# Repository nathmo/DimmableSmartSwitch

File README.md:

DimmableSmartSwitch

This repo contains the schematic and the layout for an ESP32 based
dual channel smart dimmer.
The ESP32 is intended to run under ESP-easy (a firmware that with native support of MQTT and wifi).
This smart dimmer work for Inductive and Capacitive load both in AC or DC.
The circuit is triggered on crossing zero (if the Load power supply is AC)
The circuit contains a current sensing circuitery on both channel, 2 capacitive touch input and
a microphone to stream audio for voice recognition (on another device (like a raspberry pi)) and obviously the circuitery to dim the load
A PLC transcienver may be added in futur revision
(PLC transcienver : A chip that allow to transmit data over power line)

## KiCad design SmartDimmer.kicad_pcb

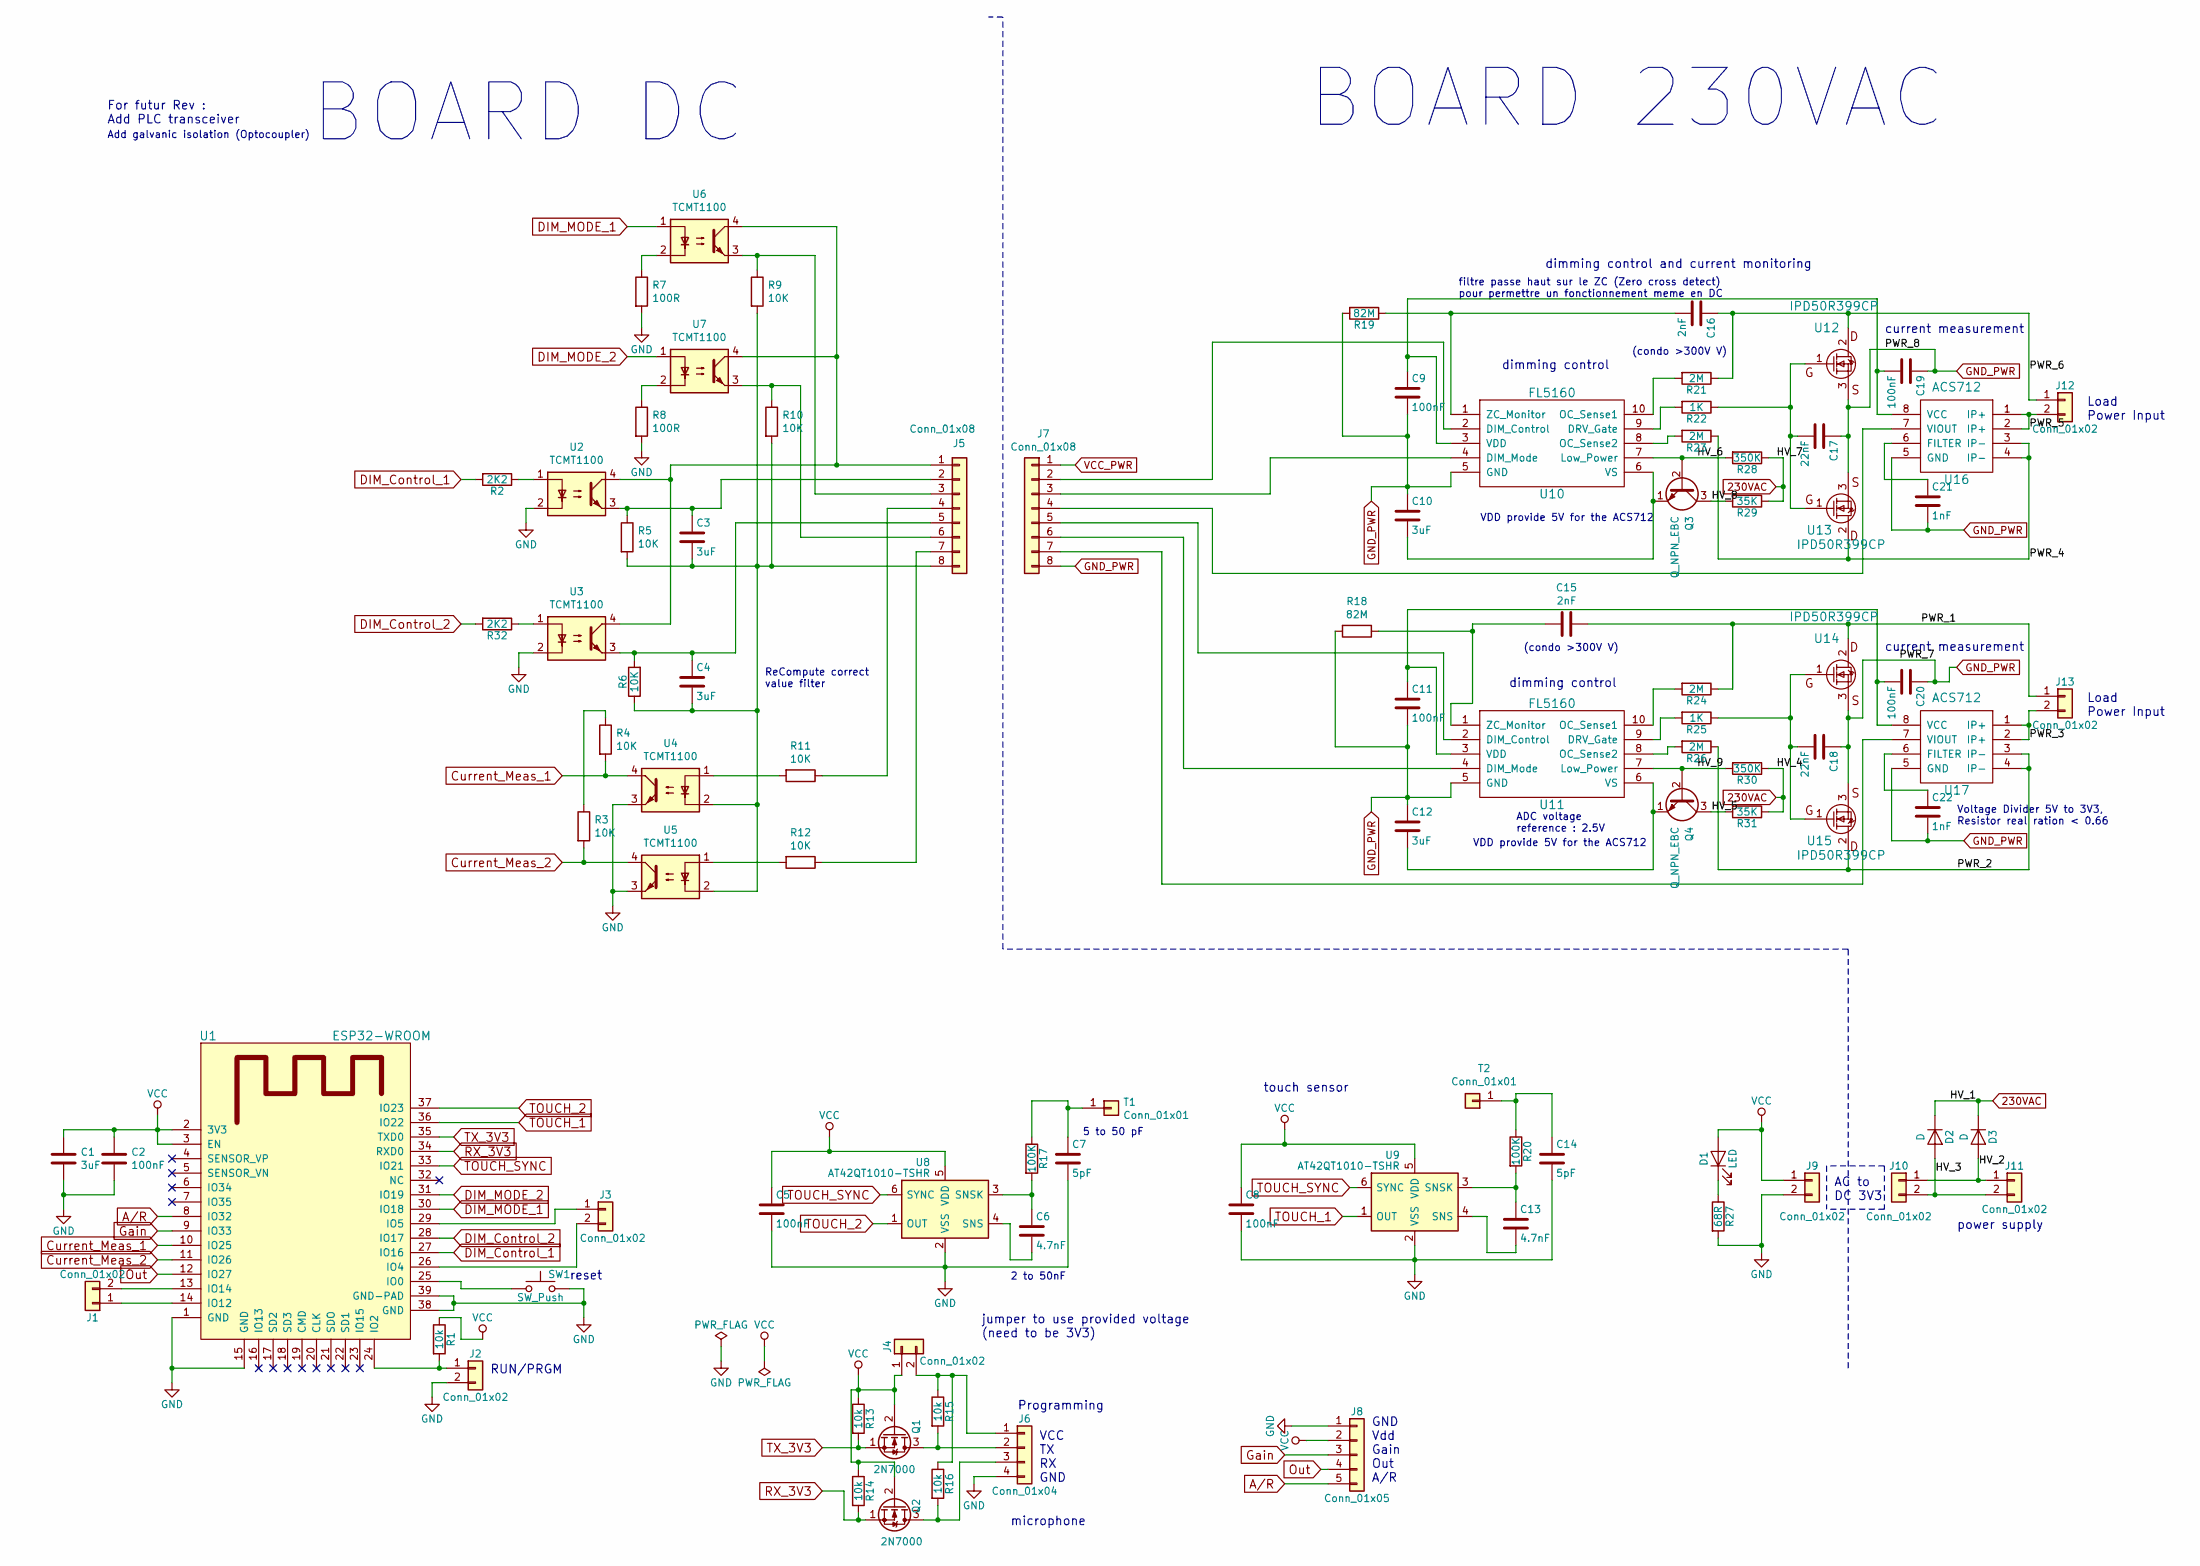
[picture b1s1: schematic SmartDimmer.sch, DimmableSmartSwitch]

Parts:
C1, C3, C4, C10, C12: 3uF; C_1206_3216Metric_Pad1.42x1.75mm_HandSolder
C2, C5, C8, C9, C11, C19, C20: 100nF; C_1206_3216Metric_Pad1.42x1.75mm_HandSolder
C6, C13: 4.7nF; C_1206_3216Metric_Pad1.42x1.75mm_HandSolder
C7, C14: 5pF; C_1206_3216Metric_Pad1.42x1.75mm_HandSolder
C15, C16: 2nF; C_1206_3216Metric_Pad1.42x1.75mm_HandSolder
C17, C18: 22nF; C_1206_3216Metric_Pad1.42x1.75mm_HandSolder
C21, C22: 1nF; C_1206_3216Metric_Pad1.42x1.75mm_HandSolder
D1: LED; LED_1206_3216Metric_Pad1.42x1.75mm_HandSolder
D2, D3: D; D_1206_3216Metric_Pad1.42x1.75mm_HandSolder
J1, J2, J3, J4, J9, J10: Conn_01x02; PinHeader_1x02_P2.54mm_Vertical
J5, J7: Conn_01x08; PinHeader_1x08_P2.54mm_Vertical
J6: Conn_01x04; PinHeader_1x04_P2.54mm_Vertical
J8: Conn_01x05; PinHeader_1x05_P2.54mm_Vertical
J11, J12, J13: Conn_01x02; TerminalBlock_RND_205-00012_1x02_P5.00mm_Horizontal
Q1, Q2: 2N7000; SOT-23_Handsoldering
Q3, Q4: Q_NPN_EBC; SOT-23_Handsoldering
R1, R13, R14, R15, R16: 10k; R_1206_3216Metric_Pad1.42x1.75mm_HandSolder
R2, R32: 2K2; R_1206_3216Metric_Pad1.42x1.75mm_HandSolder
R3, R4, R5, R6, R9, R10, R11, R12: 10K; R_1206_3216Metric_Pad1.42x1.75mm_HandSolder
R7, R8: 100R; R_1206_3216Metric_Pad1.42x1.75mm_HandSolder
R17, R20: 100K; R_1206_3216Metric_Pad1.42x1.75mm_HandSolder
R18, R19: 82M; R_1206_3216Metric_Pad1.42x1.75mm_HandSolder
R21, R23, R24, R26: 2M; R_1206_3216Metric_Pad1.42x1.75mm_HandSolder
R22, R25: 1K; R_1206_3216Metric_Pad1.42x1.75mm_HandSolder
R27: 68R; R_1206_3216Metric_Pad1.42x1.75mm_HandSolder
R28, R30: 350K; R_1206_3216Metric_Pad1.42x1.75mm_HandSolder
R29, R31: 35K; R_1206_3216Metric_Pad1.42x1.75mm_HandSolder
SW1: SW_Push; SW_SPST_PTS645
T1, T2: Conn_01x01; PinHeader_1x01_P2.54mm_Vertical
U1: ESP32-WROOM
U2, U3, U4, U5, U6, U7: TCMT1100; SOP-4_4.4x2.8mm_P1.27mm
U8, U9: AT42QT1010-TSHR; SOT-23-6
U10, U11: FL5160; SSOP-10_3.9x4.9mm_P1.00mm
U12, U13, U14, U15: IPD50R399CP; TO-252-2
U16, U17: ACS712; SOIC-8_3.9x4.9mm_P1.27mm

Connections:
230VAC: D2.1 (K), D3.1 (K), R28.1, R29.1, R30.1, R31.1
/HV_2: D3.2 (A), J10.1, J11.1
/HV_3: D2.2 (A), J10.2, J11.2
/HV_5: Q4.3 (C), R31.2
/HV_6: Q3.2 (B), R28.2, U10.7 (Low_Power)
/HV_8: Q3.3 (C), R29.2
/HV_9: Q4.2 (B), R30.2, U11.7 (Low_Power)
/PWR_1: C15.1, J13.1, R24.1, U14.2
/PWR_2: R26.1, U15.2, U17.3 (IP-), U17.4 (IP-)
/PWR_3: J13.2, U17.1 (IP+), U17.2 (IP+)
/PWR_4: R23.1, U13.2, U16.3 (IP-), U16.4 (IP-)
/PWR_5: J12.2, U16.1 (IP+), U16.2 (IP+)
/PWR_6: C16.1, J12.1, R21.1, U12.2
A/R: J8.5, U1.8 (IO32)
Current_Meas_1: R4.2, U1.10 (IO25), U4.4
Current_Meas_2: R3.2, U1.11 (IO26), U5.4
DIM_Control_1: R2.2, U1.27 (IO16)
DIM_Control_2: R32.2, U1.28 (IO17)
DIM_MODE_1: U1.30 (IO18), U6.1
DIM_MODE_2: U1.31 (IO19), U7.1
GND: C1.2, C2.2, C5.2, C7.2, C8.2, C14.2, J2.2, J6.4, J8.1, J9.2, R7.2, R8.2, R27.2, SW1.2, U1.1 (GND), U1.15 (GND), U1.38 (GND), U1.39 (GND-PAD), U2.2, U3.2, U4.3, U5.3, U8.2 (VSS), U9.2 (VSS)
GND_PWR: C9.2, C10.1, C11.2, C12.1, C17.1, C18.1, C19.1, C20.1, C21.2, C22.2, J7.8, R18.2, R19.2, U10.5 (GND), U11.5 (GND), U12.3, U13.3, U14.3, U15.3, U16.5 (GND), U17.5 (GND)
Gain: J8.3, U1.9 (IO33)
unnamed: C3.1, J5.2, R5.1, U2.3
unnamed: C3.2, C4.2, J5.8, R5.2, R6.1, R9.2, R10.2, U4.2, U5.2
unnamed: C4.1, J5.5, R6.2, U3.3
unnamed: C6.1, R17.2, U8.3 (SNSK)
unnamed: C6.2, U8.4 (SNS)
unnamed: C7.1, R17.1, T1.1
unnamed: C10.2, Q3.1 (E), U10.6 (VS)
unnamed: C11.1, C20.2, U11.3 (VDD), U17.8 (VCC)
unnamed: C12.2, Q4.1 (E), U11.6 (VS)
unnamed: C13.1, R20.2, U9.3 (SNSK)
unnamed: C13.2, U9.4 (SNS)
unnamed: C14.1, R20.1, T2.1
unnamed: C15.2, R18.1, U11.1 (ZC_Monitor)
unnamed: C16.2, R19.1, U10.1 (ZC_Monitor)
unnamed: C17.2, R22.1, U12.1, U13.1
unnamed: C18.2, R25.1, U14.1, U15.1
unnamed: C9.1, C19.2, U10.3 (VDD), U16.8 (VCC)
unnamed: C21.1, U16.6 (FILTER)
unnamed: C22.1, U17.6 (FILTER)
unnamed: D1.1 (K), R27.1
unnamed: J1.1, U1.14 (IO12)
unnamed: J1.2, U1.13 (IO14)
unnamed: J2.1, R1.2, U1.24 (IO2)
unnamed: J3.1, U1.29 (IO5)
unnamed: J3.2, U1.26 (IO4)
unnamed: J4.2, J6.1, R15.1, R16.1
unnamed: J5.1, U2.4, U3.4, U6.4, U7.4
unnamed: J5.3, R9.1, U6.3
unnamed: J5.4, R11.1
unnamed: J5.6, R10.1, U7.3
unnamed: J5.7, R12.1
unnamed: J6.2, Q1.3 (D), R15.2
unnamed: J6.3, Q2.3 (D), R16.2
unnamed: J7.2, U10.2 (DIM_Control)
unnamed: J7.3, U10.4 (DIM_Mode)
unnamed: J7.4, U16.7 (VIOUT)
unnamed: J7.5, U11.2 (DIM_Control)
unnamed: J7.6, U11.4 (DIM_Mode)
unnamed: J7.7, U17.7 (VIOUT)
unnamed: R2.1, U2.1
unnamed: R3.1, R4.1
unnamed: R7.1, U6.2
unnamed: R8.1, U7.2
unnamed: R11.2, U4.1
unnamed: R12.2, U5.1
unnamed: R21.2, U10.10 (OC_Sense1)
unnamed: R22.2, U10.9 (DRV_Gate)
unnamed: R23.2, U10.8 (OC_Sense2)
unnamed: R24.2, U11.10 (OC_Sense1)
unnamed: R25.2, U11.9 (DRV_Gate)
unnamed: R26.2, U11.8 (OC_Sense2)
unnamed: R32.1, U3.1
unnamed: SW1.1, U1.25 (IO0)
Out: J8.4, U1.12 (IO27)
RX_3V3: Q2.1 (S), R14.2, U1.34 (RXD0)
TOUCH_1: U1.36 (IO22), U9.1 (OUT)
TOUCH_2: U1.37 (IO23), U8.1 (OUT)
TOUCH_SYNC: U1.33 (IO21), U8.6 (SYNC), U9.6 (SYNC)
TX_3V3: Q1.1 (S), R13.2, U1.35 (TXD0)
VCC: C1.1, C2.1, C5.1, C8.1, D1.2 (A), J4.1, J8.2, J9.1, Q1.2 (G), Q2.2 (G), R1.1, R13.1, R14.1, U1.2 (3V3), U1.3 (EN), U8.5 (VDD), U9.5 (VDD)

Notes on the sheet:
power supply
touch sensor
Load Power Input
dimming control and current monitoring
Programming
microphone
For futur Rev : Add PLC transceiver
AC to DC 3V3
jumper to use provided voltage (need to be 3V3)
VCC TX RX GND
reset
RUN/PRGM
current measurement
dimming control
GND Vdd Gain Out A/R
filtre passe haut sur le ZC (Zero cross detect) pour permettre un fonctionnement meme en DC
(condo >300V V)
2 to 50nF
5 to 50 pF
Voltage Divider 5V to 3V3, Resistor real ration < 0.66
ADC voltage reference : 2.5V
BOARD 230VAC
BOARD DC
VDD provide 5V for the ACS712
Add galvanic isolation (Optocoupler)
ReCompute correct value filter

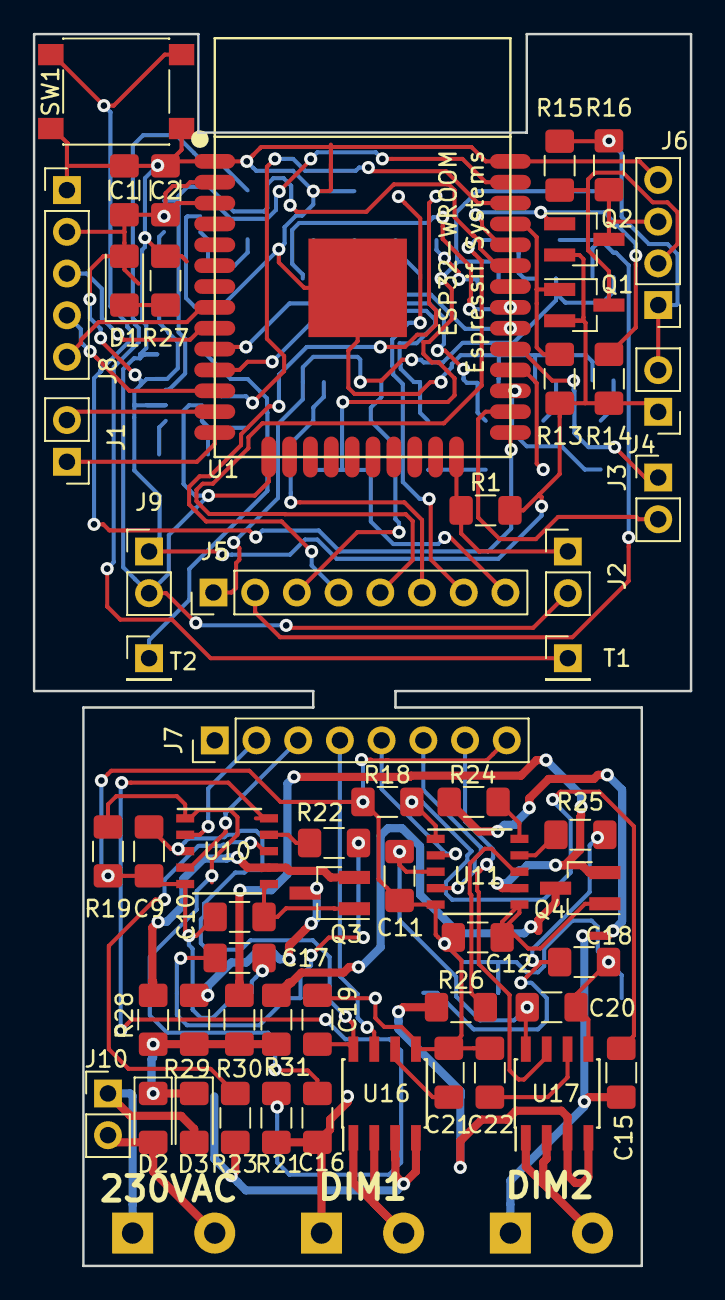
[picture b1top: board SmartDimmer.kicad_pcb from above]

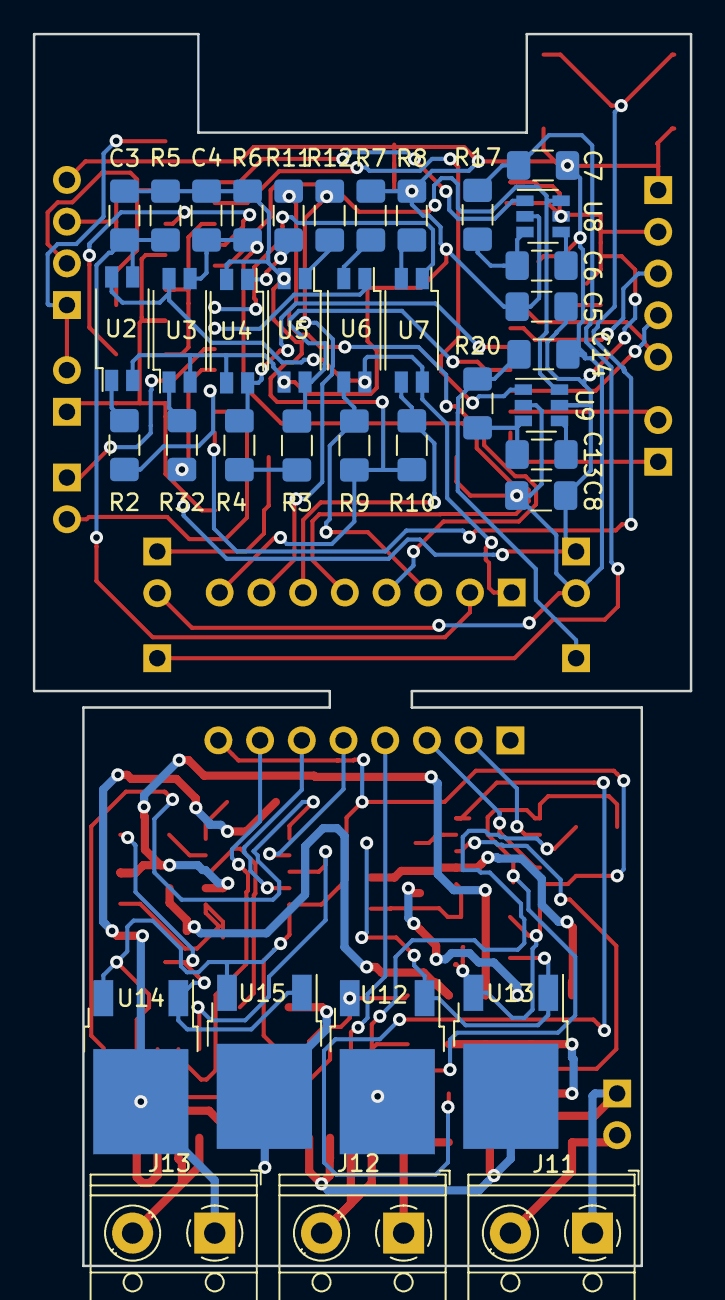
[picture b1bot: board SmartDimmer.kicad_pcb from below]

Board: 2 copper layers, 40.0 x 75.0 mm, 94 parts (37 on the bottom side), 83 nets.

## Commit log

2019-01-27 First commit, most of the component have been selected
2019-01-27 finished the shematic, the value of the component need to be calculated
2019-02-06 Schematic update
2019-02-06 added datasheet
2019-02-06 more datasheet
2019-02-10 Rework of the schematic and started the layout
2019-02-10 NewLayout
2019-02-10 RoutingDone
2019-02-10 added PDF
2019-02-10 aestetic change
2019-02-11 Update README.md
    improved the readme
